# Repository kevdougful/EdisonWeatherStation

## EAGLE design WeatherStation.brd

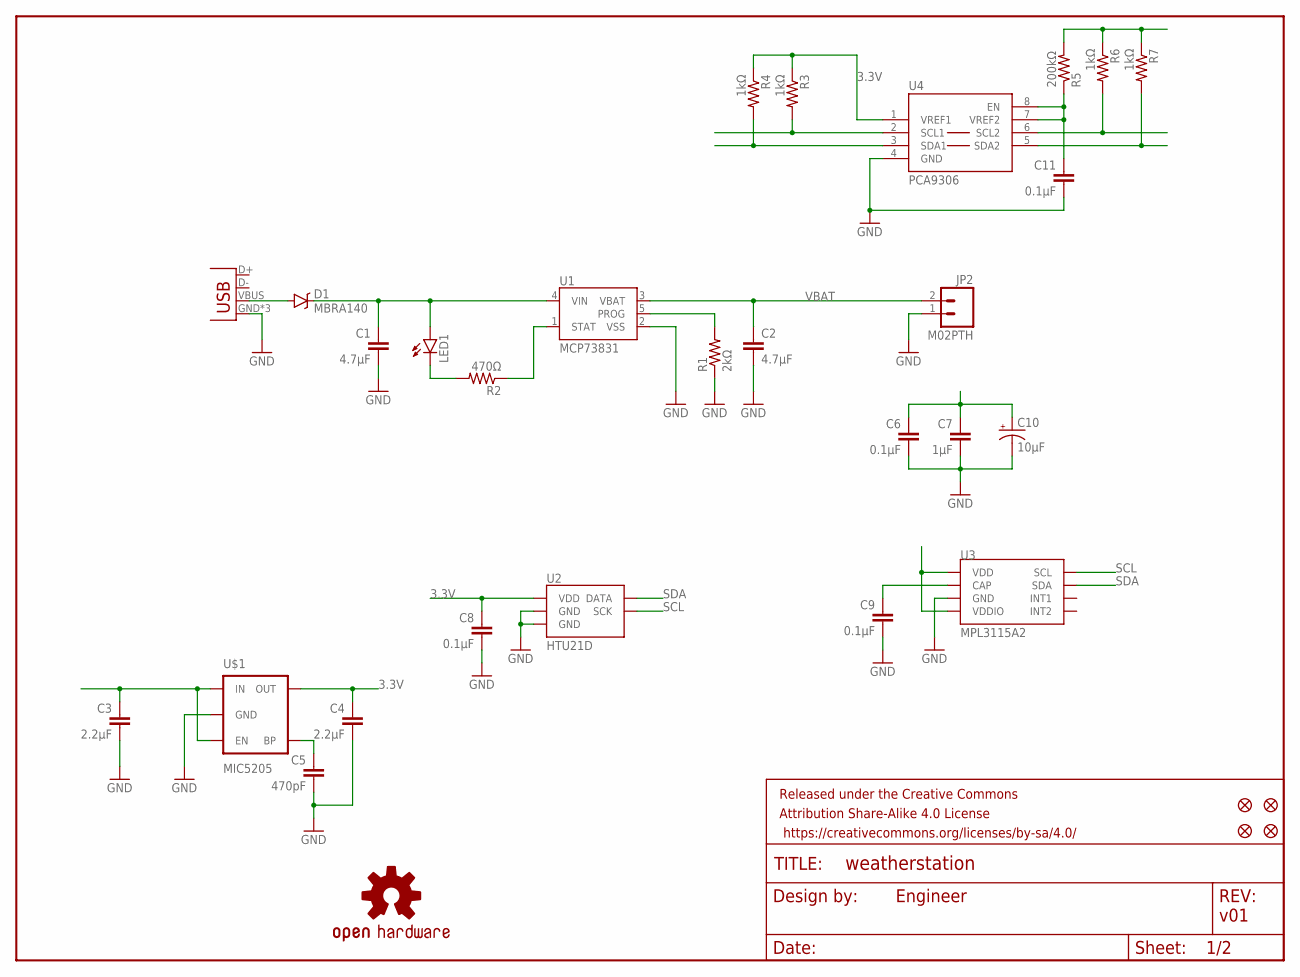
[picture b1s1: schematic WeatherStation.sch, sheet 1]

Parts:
C1, C2: 4.7µF; 0805
C3, C4: 2.2µF; 0805
C5: 470pF; 0805
C6, C8, C9, C11: 0.1µF; 0805
C7: 1µF; 0805
C10: 10µF; EIA3216
D1: MBRA140; SMA-DIODE
FID1, FID2, FID3, FID4: FIDUCIAL1X2; FIDUCIAL-1X2
FRAME1: FRAME-LETTER; CREATIVE_COMMONS
JP1: USB-MICROB
JP2: M02PTH; 1X02
LED1: LED0603; LED-0603
LOGO1: OSHW-LOGOS; OSHW-LOGO-S
R1: 2kΩ; 0603-RES
R2: 470Ω; 0603-RES
R3, R4, R6, R7: 1kΩ; 0603-RES
R5: 200kΩ; 0603-RES
U1: MCP73831; SOT23-5
U2: HTU21D
U3: MPL3115A2; LGA8
U4: PCA9306; PSOP-8
U$1: MIC5205; SOT23-5

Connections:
1.8V: R5.2, R6.1, R7.1; also elsewhere on the board
3.3V: C4.1, C6.1, C7.1, C8.1, C10.A (+), R3.1, R4.1, U2.VDD, U3.1 (VDD), U3.4 (VDDIO), U4.1 (VREF1), U$1.5 (OUT); also elsewhere on the board
GND: C1.2, C2.2, C3.2, C4.2, C5.2, C6.2, C7.2, C8.2, C9.2, C10.C (-), C11.2, JP1.GND, JP1.MT1 (GND), JP1.MT2 (GND), JP2.1, R1.1, U1.2 (VSS), U2.7 (GND), U2.GND, U3.3 (GND), U4.4 (GND), U$1.2 (GND); also elsewhere on the board
unnamed: D1.A, JP1.VBUS
unnamed: C1.1, D1.C, LED1.A, U1.4 (VIN)
unnamed: C9.1, U3.2 (CAP)
unnamed: LED1.C, R2.2
unnamed: R2.1, U1.1 (STAT)
unnamed: R1.2, U1.5 (PROG)
unnamed: C5.1, U$1.4 (BP)
unnamed: C11.1, R5.1, U4.7 (VREF2), U4.8 (EN)
unnamed: R6.2, U4.6 (SCL2)
unnamed: R7.2, U4.5 (SDA2)
SCL: R3.2, U2.SCK, U3.8 (SCL), U4.2 (SCL1)
SDA: R4.2, U2.DATA, U3.7 (SDA), U4.3 (SDA1)
VBAT: C2.1, C3.1, JP2.2, U1.3 (VBAT), U$1.1 (IN), U$1.3 (EN)

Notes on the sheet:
v01
Engineer

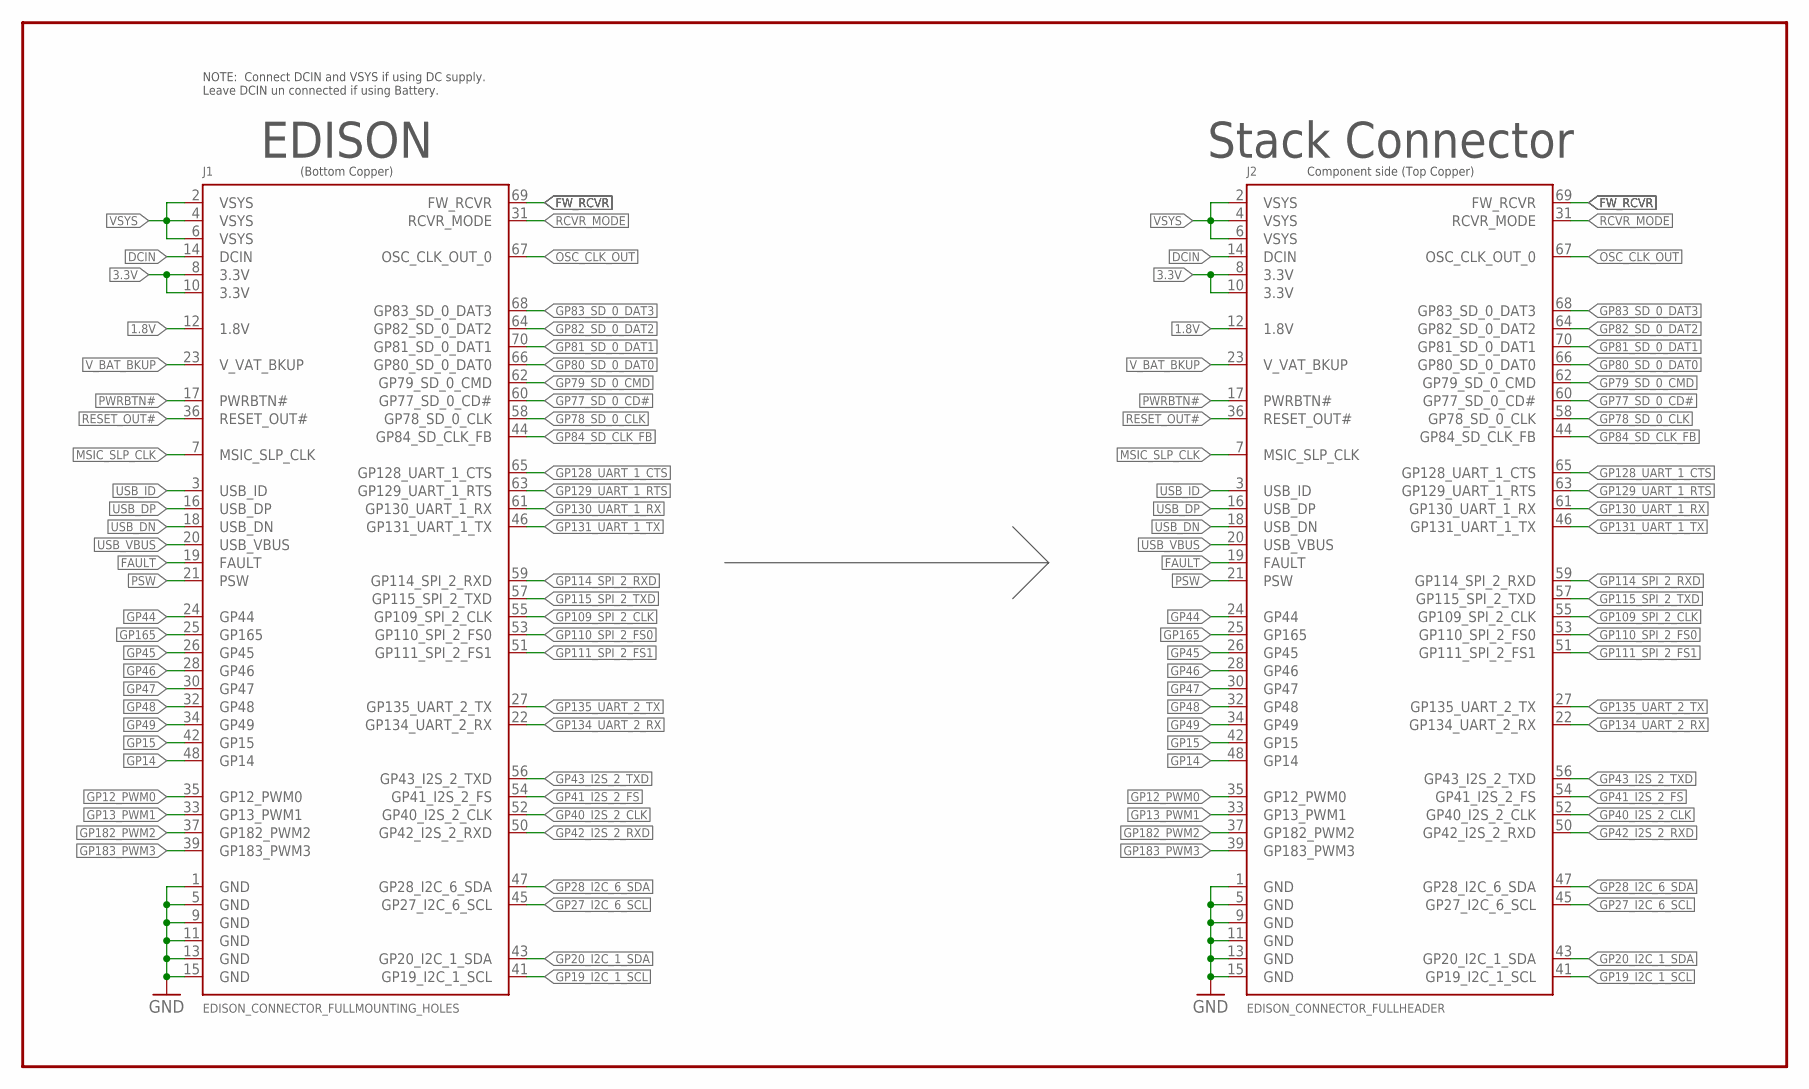
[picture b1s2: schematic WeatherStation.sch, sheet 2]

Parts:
J1: EDISON_CONNECTOR_FULLMOUNTING_HOLES; EDISON_DAUGHTER
J2: EDISON_CONNECTOR_FULLHEADER; DF40C-70DP-0.4(51)

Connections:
1.8V: J1.12 (1.8V), J2.12 (1.8V); also elsewhere on the board
3.3V: J1.8 (3.3V), J1.10 (3.3V), J2.8 (3.3V), J2.10 (3.3V); also elsewhere on the board
DCIN: J1.14 (DCIN), J2.14 (DCIN)
FAULT: J1.19 (FAULT), J2.19 (FAULT)
FW_RCVR: J1.69 (FW_RCVR), J2.69 (FW_RCVR)
GND: J1.1 (GND), J1.5 (GND), J1.9 (GND), J1.11 (GND), J1.13 (GND), J1.15 (GND), J2.1 (GND), J2.5 (GND), J2.9 (GND), J2.11 (GND), J2.13 (GND), J2.15 (GND); also elsewhere on the board
GP12_PWM0: J1.35 (GP12_PWM0), J2.35 (GP12_PWM0)
GP13_PWM1: J1.33 (GP13_PWM1), J2.33 (GP13_PWM1)
GP14: J1.48 (GP14), J2.48 (GP14)
GP15: J1.42 (GP15), J2.42 (GP15)
GP19_I2C_1_SCL: J1.41 (GP19_I2C_1_SCL), J2.41 (GP19_I2C_1_SCL)
GP20_I2C_1_SDA: J1.43 (GP20_I2C_1_SDA), J2.43 (GP20_I2C_1_SDA)
GP27_I2C_6_SCL: J1.45 (GP27_I2C_6_SCL), J2.45 (GP27_I2C_6_SCL)
GP28_I2C_6_SDA: J1.47 (GP28_I2C_6_SDA), J2.47 (GP28_I2C_6_SDA)
GP40_I2S_2_CLK: J1.52 (GP40_I2S_2_CLK), J2.52 (GP40_I2S_2_CLK)
GP41_I2S_2_FS: J1.54 (GP41_I2S_2_FS), J2.54 (GP41_I2S_2_FS)
GP42_I2S_2_RXD: J1.50 (GP42_I2S_2_RXD), J2.50 (GP42_I2S_2_RXD)
GP43_I2S_2_TXD: J1.56 (GP43_I2S_2_TXD), J2.56 (GP43_I2S_2_TXD)
GP44: J1.24 (GP44), J2.24 (GP44)
GP45: J1.26 (GP45), J2.26 (GP45)
GP46: J1.28 (GP46), J2.28 (GP46)
GP47: J1.30 (GP47), J2.30 (GP47)
GP48: J1.32 (GP48), J2.32 (GP48)
GP49: J1.34 (GP49), J2.34 (GP49)
GP77_SD_0_CD#: J1.60 (GP77_SD_0_CD#), J2.60 (GP77_SD_0_CD#)
GP78_SD_0_CLK: J1.58 (GP78_SD_0_CLK), J2.58 (GP78_SD_0_CLK)
GP79_SD_0_CMD: J1.62 (GP79_SD_0_CMD), J2.62 (GP79_SD_0_CMD)
GP80_SD_0_DAT0: J1.66 (GP80_SD_0_DAT0), J2.66 (GP80_SD_0_DAT0)
GP81_SD_0_DAT1: J1.70 (GP81_SD_0_DAT1), J2.70 (GP81_SD_0_DAT1)
GP82_SD_0_DAT2: J1.64 (GP82_SD_0_DAT2), J2.64 (GP82_SD_0_DAT2)
GP83_SD_0_DAT3: J1.68 (GP83_SD_0_DAT3), J2.68 (GP83_SD_0_DAT3)
GP84_SD_CLK_FB: J1.44 (GP84_SD_CLK_FB), J2.44 (GP84_SD_CLK_FB)
GP109_SPI_2_CLK: J1.55 (GP109_SPI_2_CLK), J2.55 (GP109_SPI_2_CLK)
GP110_SPI_2_FS0: J1.53 (GP110_SPI_2_FS0), J2.53 (GP110_SPI_2_FS0)
GP111_SPI_2_FS1: J1.51 (GP111_SPI_2_FS1), J2.51 (GP111_SPI_2_FS1)
GP114_SPI_2_RXD: J1.59 (GP114_SPI_2_RXD), J2.59 (GP114_SPI_2_RXD)
GP115_SPI_2_TXD: J1.57 (GP115_SPI_2_TXD), J2.57 (GP115_SPI_2_TXD)
GP128_UART_1_CTS: J1.65 (GP128_UART_1_CTS), J2.65 (GP128_UART_1_CTS)
GP129_UART_1_RTS: J1.63 (GP129_UART_1_RTS), J2.63 (GP129_UART_1_RTS)
GP130_UART_1_RX: J1.61 (GP130_UART_1_RX), J2.61 (GP130_UART_1_RX)
GP131_UART_1_TX: J1.46 (GP131_UART_1_TX), J2.46 (GP131_UART_1_TX)
GP134_UART_2_RX: J1.22 (GP134_UART_2_RX), J2.22 (GP134_UART_2_RX)
GP135_UART_2_TX: J1.27 (GP135_UART_2_TX), J2.27 (GP135_UART_2_TX)
GP165: J1.25 (GP165), J2.25 (GP165)
GP182_PWM2: J1.37 (GP182_PWM2), J2.37 (GP182_PWM2)
GP183_PWM3: J1.39 (GP183_PWM3), J2.39 (GP183_PWM3)
MSIC_SLP_CLK: J1.7 (MSIC_SLP_CLK), J2.7 (MSIC_SLP_CLK)
OSC_CLK_OUT: J1.67 (OSC_CLK_OUT_0), J2.67 (OSC_CLK_OUT_0)
PSW: J1.21 (PSW), J2.21 (PSW)
PWRBTN#: J1.17 (PWRBTN#), J2.17 (PWRBTN#)
RCVR_MODE: J1.31 (RCVR_MODE), J2.31 (RCVR_MODE)
RESET_OUT#: J1.36 (RESET_OUT#), J2.36 (RESET_OUT#)
USB_DN: J1.18 (USB_DN), J2.18 (USB_DN)
USB_DP: J1.16 (USB_DP), J2.16 (USB_DP)
USB_ID: J1.3 (USB_ID), J2.3 (USB_ID)
USB_VBUS: J1.20 (USB_VBUS), J2.20 (USB_VBUS)
VSYS: J1.2 (VSYS), J1.4 (VSYS), J1.6 (VSYS), J2.2 (VSYS), J2.4 (VSYS), J2.6 (VSYS)
V_BAT_BKUP: J1.23 (V_VAT_BKUP), J2.23 (V_VAT_BKUP)

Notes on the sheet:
EDISON
Stack Connector
Component side (Top Copper)
(Bottom Copper)
NOTE: Connect DCIN and VSYS if using DC supply. Leave DCIN un connected if using Battery.

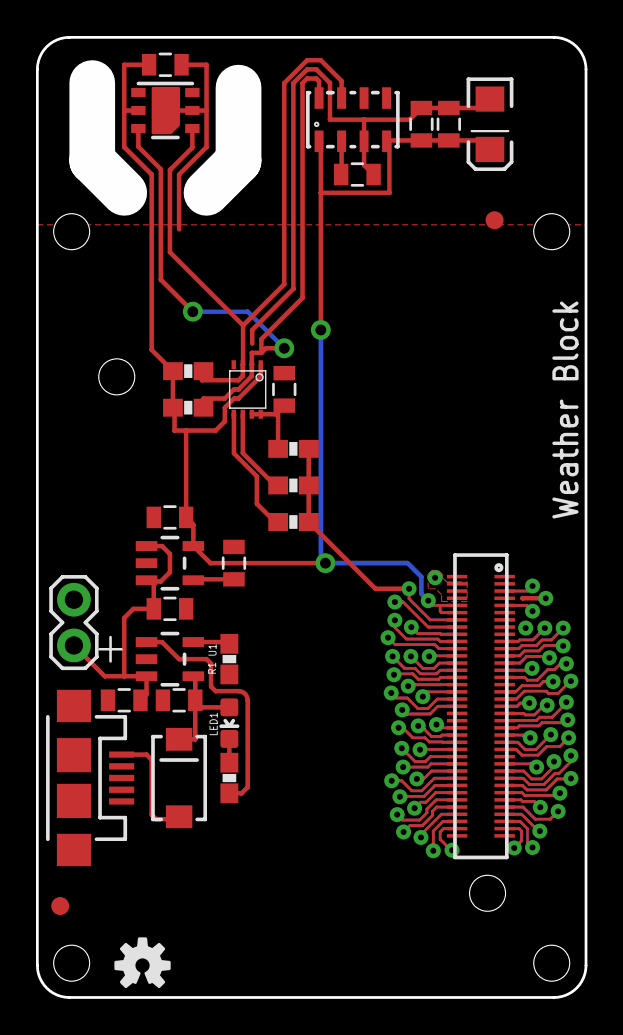
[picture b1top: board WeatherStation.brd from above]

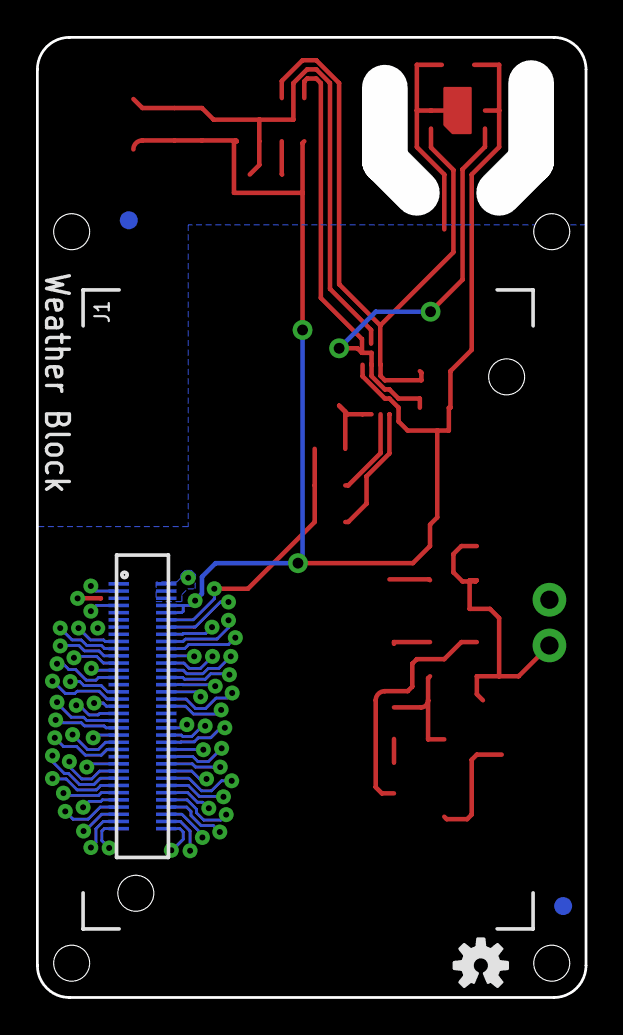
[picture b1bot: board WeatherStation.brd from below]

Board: 2 copper layers, 30.5 x 53.3 mm, 36 parts (5 on the bottom side), 71 nets.

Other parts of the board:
LOGO2: OSHW-LOGOS; OSHW-LOGO-S

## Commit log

2014-12-09 :boom::camel: Added .gitattributes & .gitignore files
2014-12-09 renamed eagle files
2014-12-09 added MCP73831 circuit
2014-12-09 added 0.1" 2-pin battery header
2014-12-10 moved a ground trace farther away from USB pads
2014-12-11 extended board length
2014-12-11 moved charge circuit and cleaned up some
2014-12-11 placed HTU21D, MPL3115A2, MIC5205-3.3V, PCA9306
    RH/temp, barometric pressure/temp, LDO voltage regulator and 1.8-3.3V
    logic level shifter.
2014-12-13 connected schematic for HTU21D
2014-12-13 connected schematic for MPL3115A2 and traces for HTU21D
2014-12-13 set and drew traces for MPL3115A2
2014-12-13 set and drew traces for MIC5205
2014-12-13 drew traces for PCA9306
2014-12-13 drew the rest of the i2c traces
2014-12-13 redrew GND planes to exclude sensor areas
2014-12-13 rearranged silkscreens
2014-12-13 rearranged silkscreens/labels
2014-12-13 removed unnecessary GND trace and via
2014-12-13 moved bottom GND plane out of antenna keep out
2014-12-19 angled some right angled traces
2014-12-19 added parts list
2014-12-19 corrected values

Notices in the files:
parts and their libraries:
SparkFun-Aesthetics: Licensing: Creative Commons ShareAlike 4.0 International - https://creativecommons.org/licenses/by-sa/4.0
SparkFun-Aesthetics: Released under the Creative Commons Attribution Share-Alike 4.0 License
SparkFun-Aesthetics: https://creativecommons.org/licenses/by-sa/4.0
